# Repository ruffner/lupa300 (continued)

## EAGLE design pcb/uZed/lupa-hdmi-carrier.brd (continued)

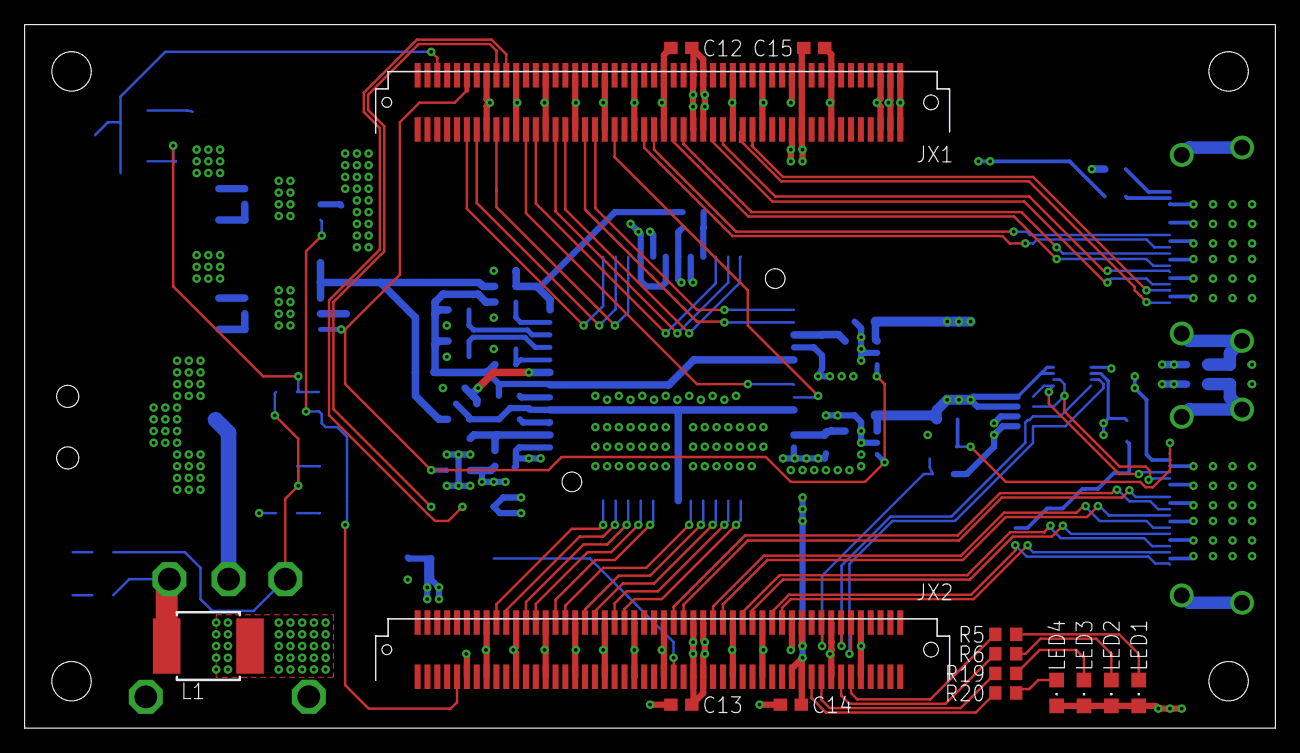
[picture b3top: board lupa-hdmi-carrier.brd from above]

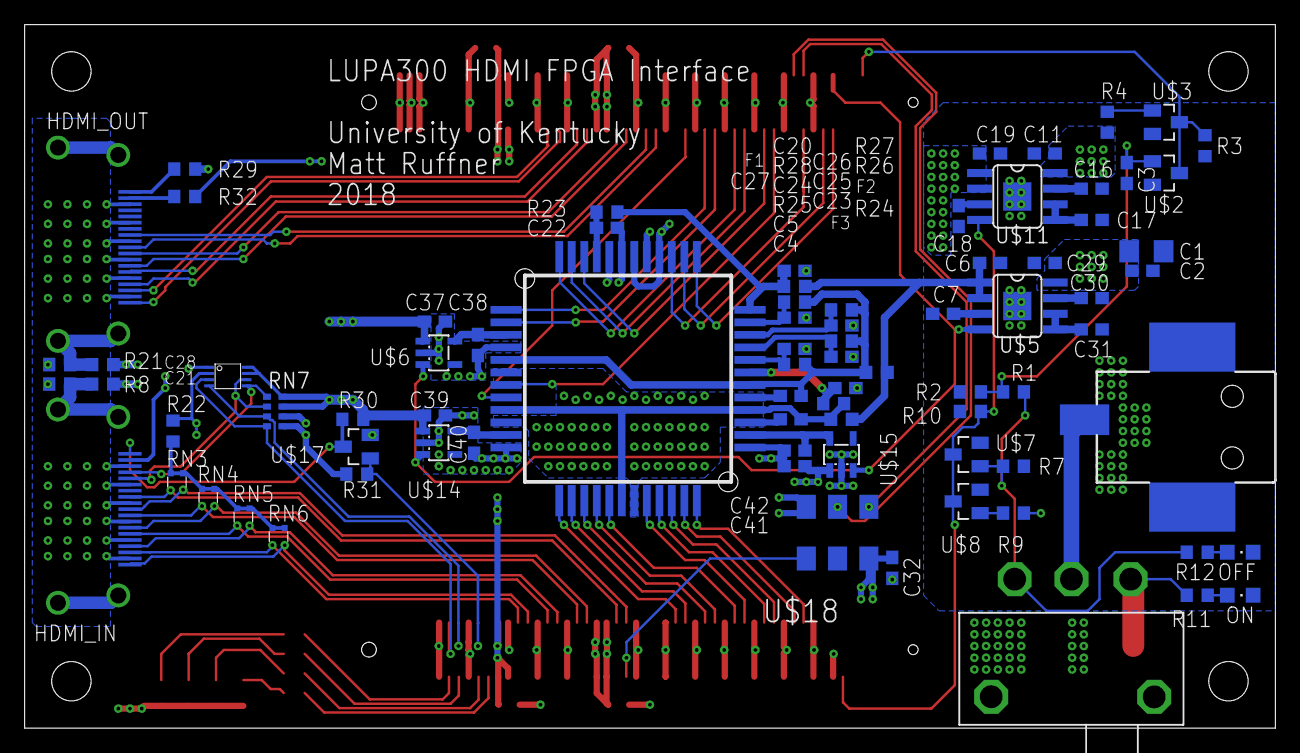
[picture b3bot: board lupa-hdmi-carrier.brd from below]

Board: 4 copper layers, 101.6 x 57.1 mm, 95 parts (80 on the bottom side), 91 nets.

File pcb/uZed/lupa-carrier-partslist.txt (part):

Partlist

Exported from lupa-carrier.sch at 7/17/2018 12:01 PM

EAGLE Version 9.0.1 Copyright (c) 1988-2018 Autodesk, Inc.

Assembly variant: 

Part     Value                   Device                  Package      Library                                                          Sheet

C1       22uF                    C-USC1206               C1206        rcl                                                              2
C2       .1uF                    C-USC0603               C0603        rcl                                                              2
C3       .1uF                    C-USC0603               C0603        rcl                                                              2
C4       1uF                     C-USC0603               C0603        rcl                                                              4
C5       1uF                     C-USC0603               C0603        rcl                                                              4
C6       10uF                    C-USC0603               C0603        rcl                                                              4
C7       1uF                     C-USC0603               C0603        rcl                                                              4
C8       .1uF                    C-USC0603               C0603        rcl                                                              2
C9       .1uF                    C-USC0603               C0603        rcl                                                              2
C10      .1uF                    C-USC0603               C0603        rcl                                                              2
C11      10uF                    C-USC0603               C0603        rcl                                                              2
C12      .1uF                    C-USC0603               C0603        rcl                                                              1
C13      .1uF                    C-USC0603               C0603        rcl                                                              1
C14      .1uF                    C-USC0603               C0603        rcl                                                              1
C15      .1uF                    C-USC0603               C0603        rcl                                                              1
C16      1uF                     C-USC0603               C0603        rcl                                                              2
C17      1uF                     C-USC0603               C0603        rcl                                                              2
C18      1uF                     C-USC0603               C0603        rcl                                                              2
C19      10uF                    C-USC0603               C0603        rcl                                                              2
C20      1uF                     C-USC0603               C0603        rcl                                                              4
C22      .1uF                    C-EUC0603               C0603        rcl                                                              3
C23      .1uF                    C-EUC0603               C0603        rcl                                                              3
C24      .1uf                    C-EUC0603               C0603        rcl                                                              3
C25      .1uf                    C-EUC0603               C0603        rcl                                                              3
C26      .1uF                    C-EUC0603               C0603        rcl                                                              3
C27      .1uF                    C-EUC0603               C0603        rcl                                                              3
C29      10uF                    C-USC0603               C0603        rcl                                                              4
C30      1uF                     C-USC0603               C0603        rcl                                                              4
C31      1uF                     C-USC0603               C0603        rcl                                                              4
C37      1uF                     C-USC0603               C0603        rcl                                                              4
C38      1uF                     C-USC0603               C0603        rcl                                                              4
C39      1uF                     C-USC0603               C0603        rcl                                                              4
C40      1uF                     C-USC0603               C0603        rcl                                                              4
C41      1uF                     C-USC0603               C0603        rcl                                                              4
C42      1uF                     C-USC0603               C0603        rcl                                                              4
FR_VAL   TPTP08R                 TPTP08R                 TP08R        testpad                                                          3
INT1     TPTP08R                 TPTP08R                 TP08R        testpad                                                          3
INT2     TPTP08R                 TPTP08R                 TP08R        testpad                                                          3
INT3     TPTP08R                 TPTP08R                 TP08R        testpad                                                          3
JX1      BERGSTAK-100POS         BERGSTAK-100POS         BERG100POS   lupa300-components                                               1
JX2      BERGSTAK-100POS         BERGSTAK-100POS         BERG100POS   lupa300-components                                               1
K1       694108105102            694108105102            694108105102 Wurth_Elektronik_Electromechanic_DC_Power_Jack_Connectors_rev15c 2
LED1                             LEDCHIPLED_0805         CHIPLED_0805 led                                                              1
LED2                             LEDCHIPLED_0805         CHIPLED_0805 led                                                              1
LED3                             LEDCHIPLED_0805         CHIPLED_0805 led                                                              1
LED4                             LEDCHIPLED_0805         CHIPLED_0805 led                                                              1
LN_VAL   TPTP08R                 TPTP08R                 TP08R        testpad                                                          3
POW_EN   TPTP08R                 TPTP08R                 TP08R        testpad                                                          1
R1       1k                      R-US_R0603              R0603        rcl                                                              2
R2       3k92                    R-US_R0603              R0603        rcl                                                              2
R3       430                     R-US_R0603              R0603        rcl                                                              2
R4       680                     R-US_R0603              R0603        rcl                                                              2
R5       330                     R-US_R0603              R0603        resistor                                                         1
R6       330                     R-US_R0603              R0603        resistor                                                         1
R7       3k92                    R-US_R0603              R0603        rcl                                                              2
R9       220                     R-US_R0603              R0603        rcl                                                              2
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
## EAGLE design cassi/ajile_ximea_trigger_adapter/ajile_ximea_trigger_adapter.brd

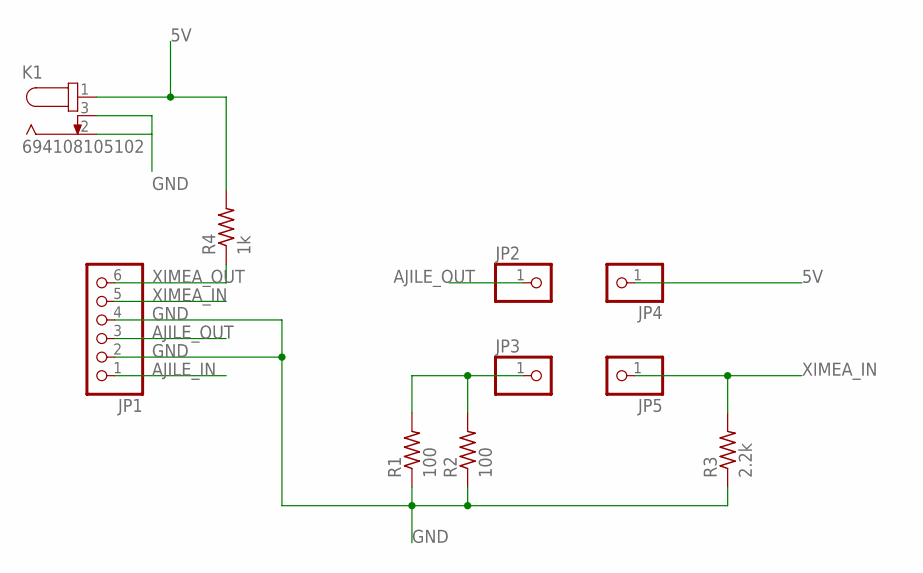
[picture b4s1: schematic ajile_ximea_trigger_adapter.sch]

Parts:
JP1: PINHD-1X6; 1X06
JP2, JP3, JP4, JP5: PINHD-1X1; 1X01
K1: 694108105102
R1, R2: 100; 0204/7
R3: 2.2k; 0204/7
R4: 1k; 0204/7

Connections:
5V: JP4.1, K1.1, R4.2
AJILE_IN: JP1.1
AJILE_OUT: JP1.3, JP2.1
GND: JP1.2, JP1.4, K1.2, K1.3, R1.1, R2.1, R3.1
unnamed: JP3.1, R1.2, R2.2
XIMEA_IN: JP1.5, JP5.1, R3.2
XIMEA_OUT: JP1.6, R4.1

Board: 2 copper layers, 10 parts (0 on the bottom side), 6 nets, no tracks yet.

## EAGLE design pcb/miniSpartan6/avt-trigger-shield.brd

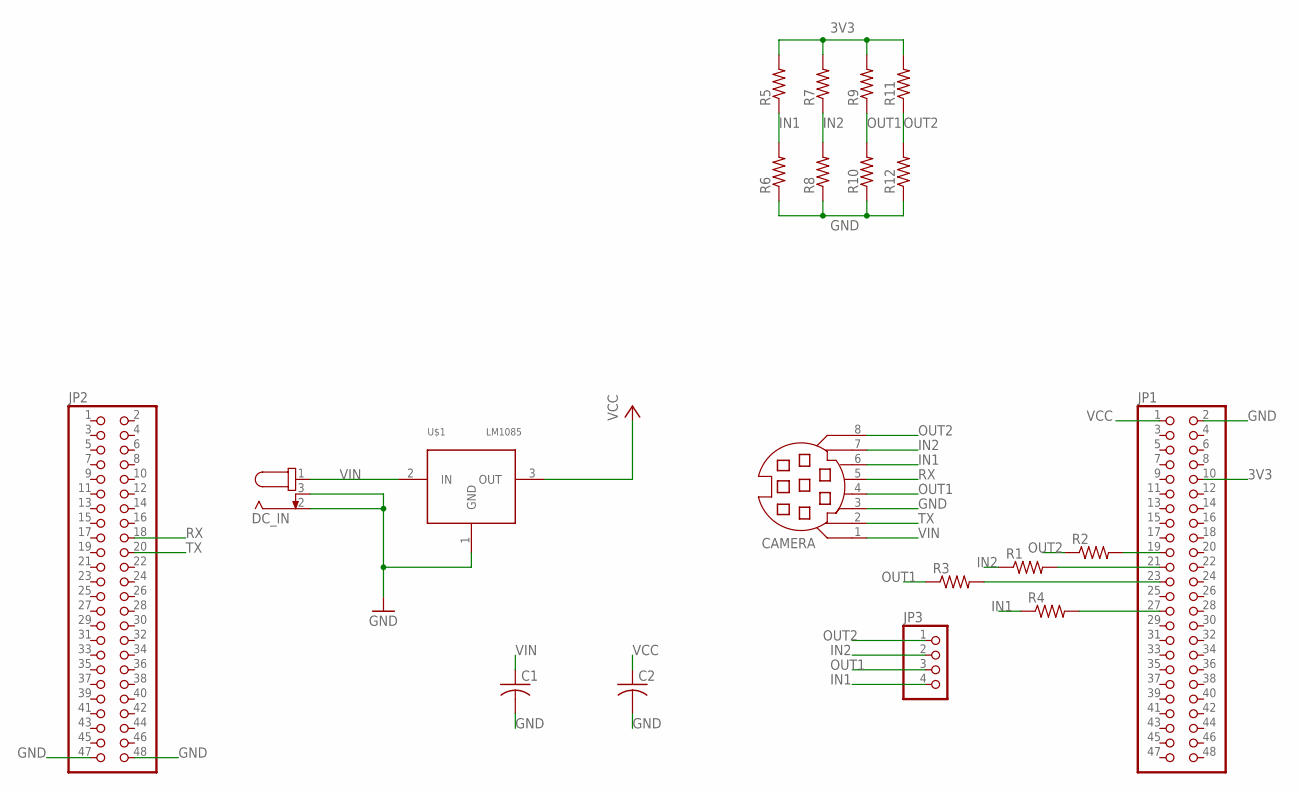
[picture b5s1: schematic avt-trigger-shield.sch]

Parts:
C1, C2: C-USC1206; C1206
CAMERA: MD08SS; MDIN08SS
DC_IN: 694106105102
JP1, JP2: PINHD-2X24; 2X24
JP3: PINHD-1X4; 1X04
R1, R2, R3, R4, R5, R6, R7, R8, R9, R10, R11, R12: R-US_R0603; R0603
U$1: LM1085; TO263

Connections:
3V3: JP1.10, R5.2, R7.2, R9.2, R11.2
GND: C1.2, C2.2, CAMERA.3, DC_IN.2, DC_IN.3, JP1.2, JP2.47, JP2.48, R6.1, R8.1, R10.1, R12.1, U$1.1 (GND)
IN1: CAMERA.6, JP3.4, R4.1, R5.1, R6.2
IN2: CAMERA.7, JP3.2, R1.1, R7.1, R8.2
unnamed: JP1.21, R1.2
unnamed: JP1.19, R2.2
unnamed: JP1.23, R3.2
unnamed: JP1.27, R4.2
OUT1: CAMERA.4, JP3.3, R3.1, R9.1, R10.2
OUT2: CAMERA.8, JP3.1, R2.1, R11.1, R12.2
RX: CAMERA.5, JP2.18
TX: CAMERA.2, JP2.20
VCC: C2.1, JP1.1, U$1.3 (OUT)
VIN: C1.1, CAMERA.1, DC_IN.1, U$1.2 (IN)

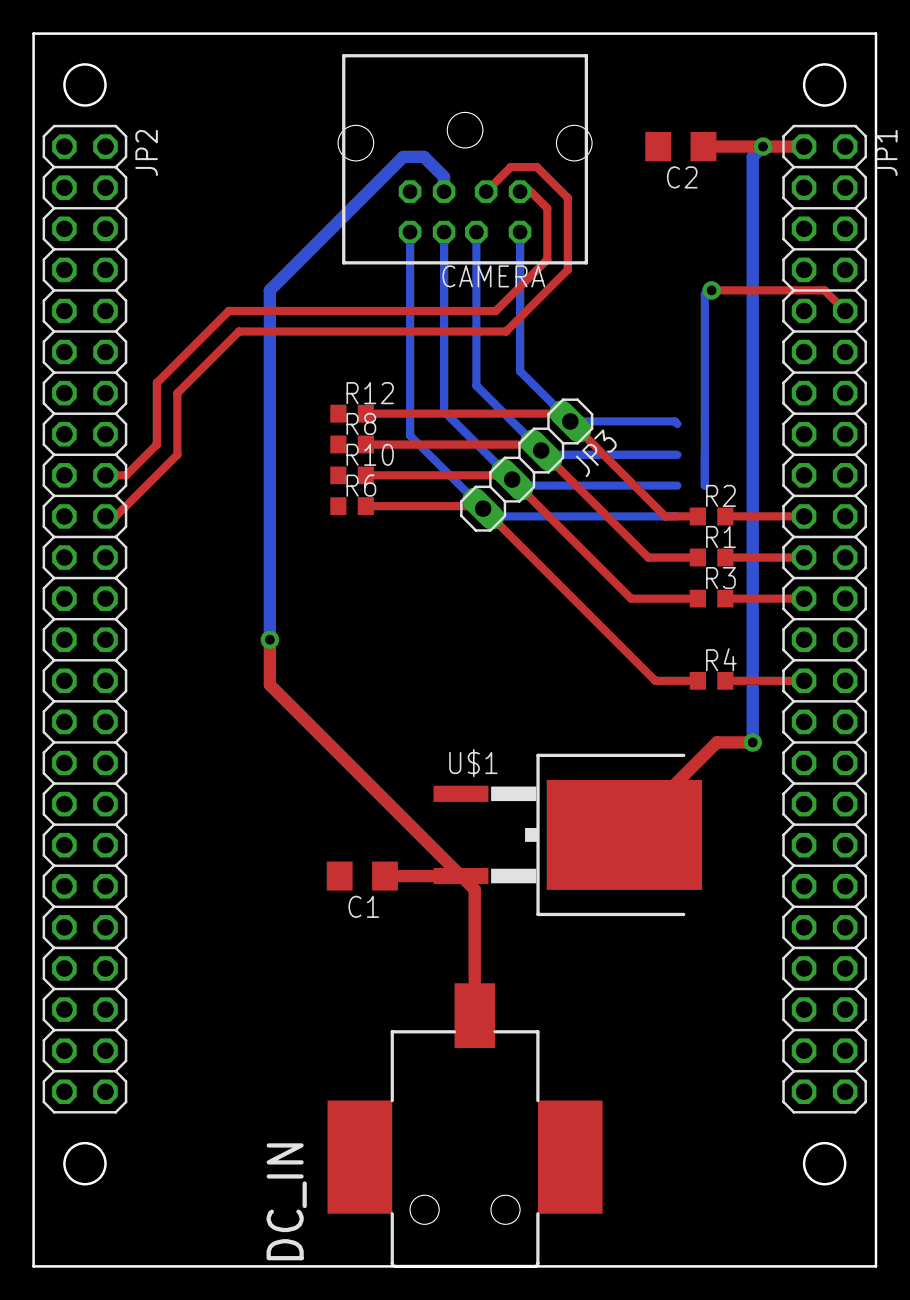
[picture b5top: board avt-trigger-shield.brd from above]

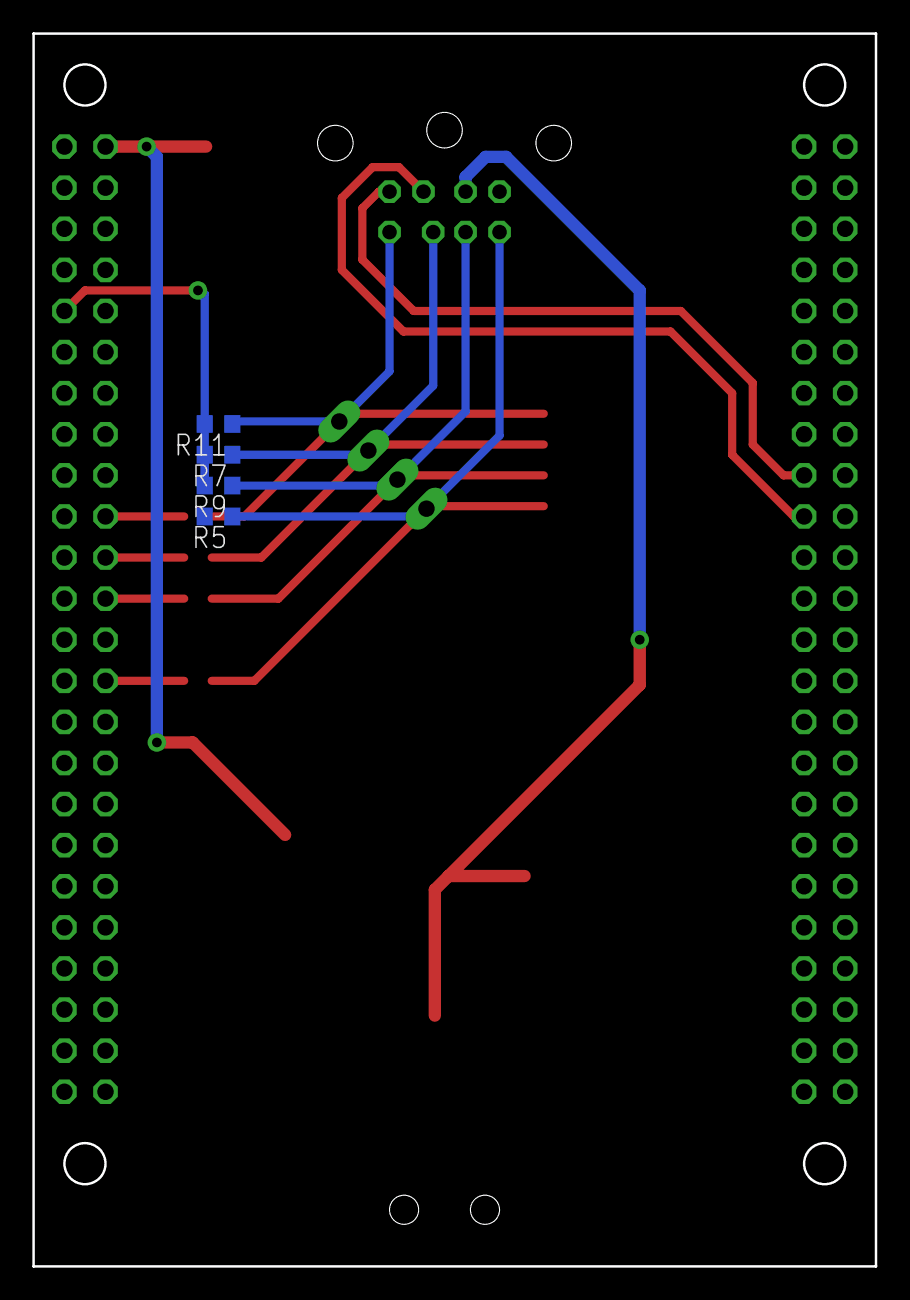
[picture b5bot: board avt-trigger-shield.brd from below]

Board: 2 copper layers, 52.1 x 76.2 mm, 20 parts (4 on the bottom side), 14 nets.

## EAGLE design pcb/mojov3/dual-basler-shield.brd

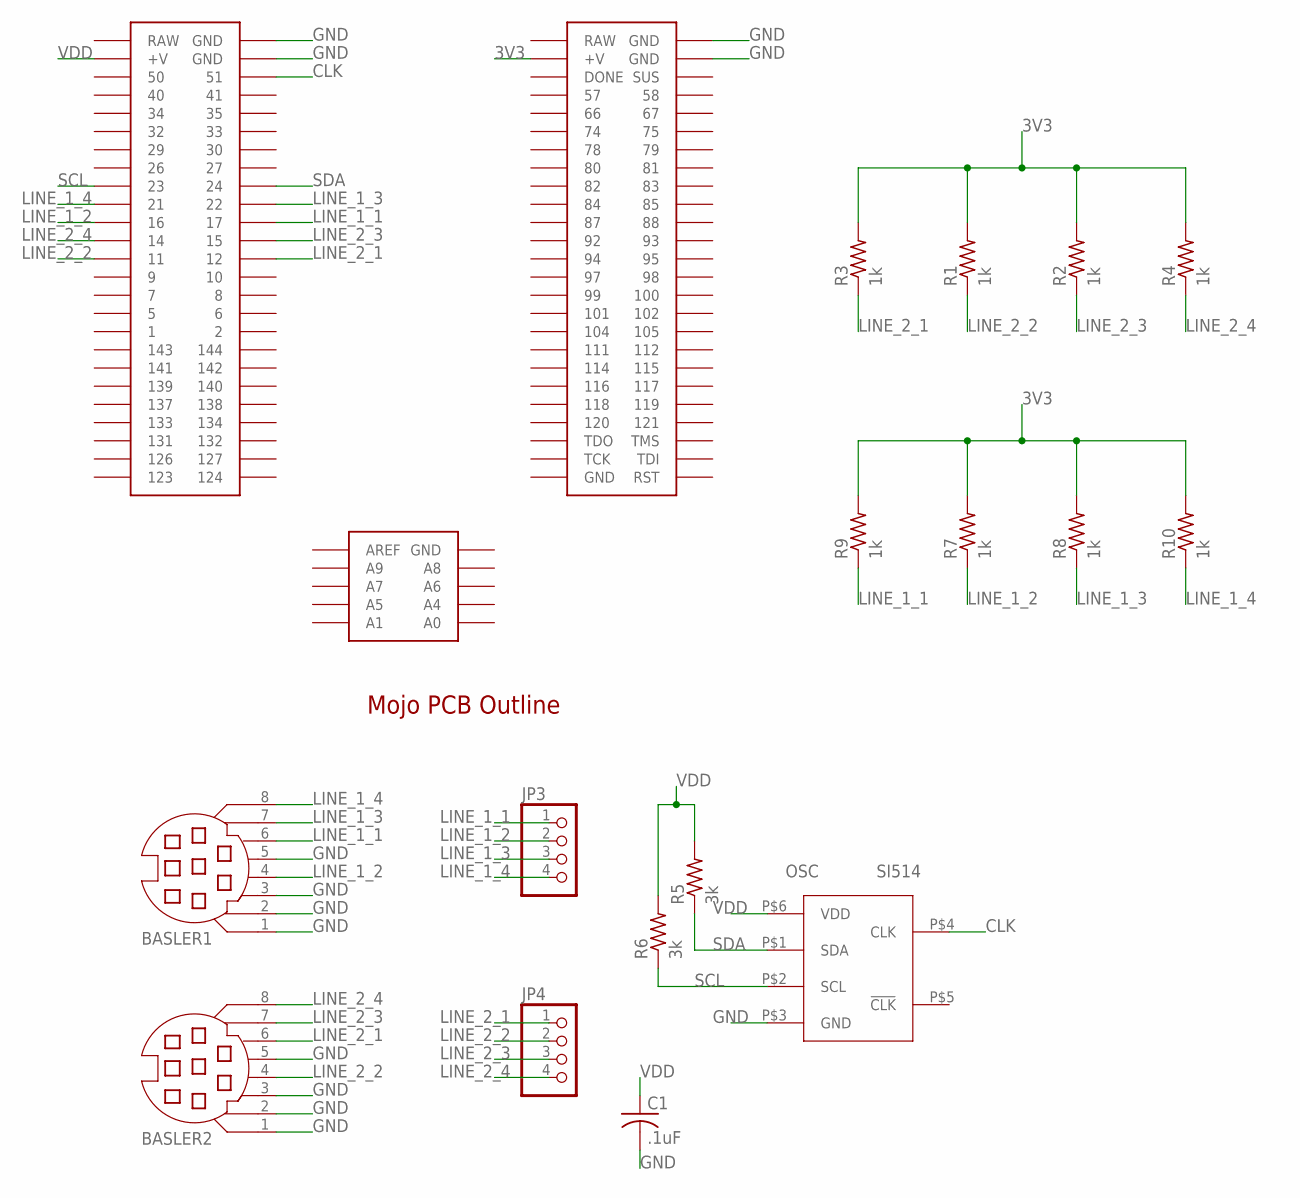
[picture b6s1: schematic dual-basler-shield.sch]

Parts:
BASLER1, BASLER2: MD08SS; MDIN08SS
C1: .1uF; C0603
JP3, JP4: PINHD-1X4; 1X04
OSC: SI514; XTAL-6PIN
R1, R2, R3, R4, R7, R8, R9, R10: 1k; R0603
R5, R6: 3k; R0603
U$3: MOJO_OUTLINE
U$4: MOJOV3; MOJO_V3

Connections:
3V3: R1.2, R2.2, R3.2, R4.2, R7.2, R8.2, R9.2, R10.2, U$4.V@2 (+V)
CLK: OSC.P$4 (CLK), U$4.51
GND: BASLER1.1, BASLER1.2, BASLER1.3, BASLER1.5, BASLER2.1, BASLER2.2, BASLER2.3, BASLER2.5, C1.2, OSC.P$3 (GND), U$4.GND@1 (GND), U$4.GND@2 (GND), U$4.GND@3 (GND), U$4.GND@4 (GND)
LINE_1_1: BASLER1.6, JP3.1, R9.1, U$4.17
LINE_1_2: BASLER1.4, JP3.2, R7.1, U$4.16
LINE_1_3: BASLER1.7, JP3.3, R8.1, U$4.22
LINE_1_4: BASLER1.8, JP3.4, R10.1, U$4.21
LINE_2_1: BASLER2.6, JP4.1, R3.1, U$4.12
LINE_2_2: BASLER2.4, JP4.2, R1.1, U$4.11
LINE_2_3: BASLER2.7, JP4.3, R2.1, U$4.15
LINE_2_4: BASLER2.8, JP4.4, R4.1, U$4.14
SCL: OSC.P$2 (SCL), R6.1, U$4.23
SDA: OSC.P$1 (SDA), R5.1, U$4.24
VDD: C1.1, OSC.P$6 (VDD), R5.2, R6.2, U$4.V@1 (+V)

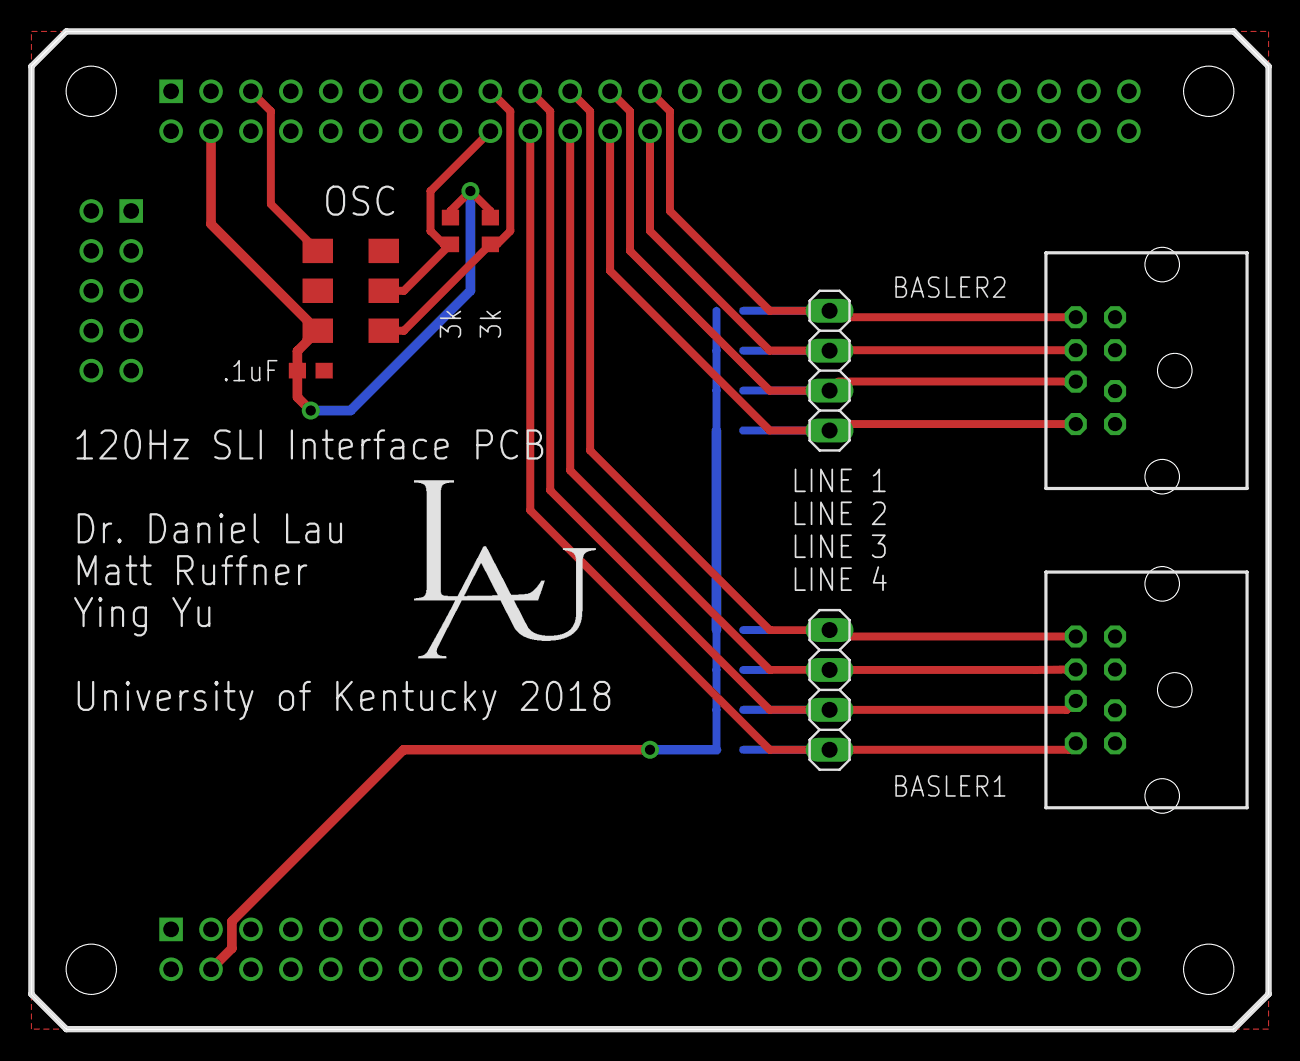
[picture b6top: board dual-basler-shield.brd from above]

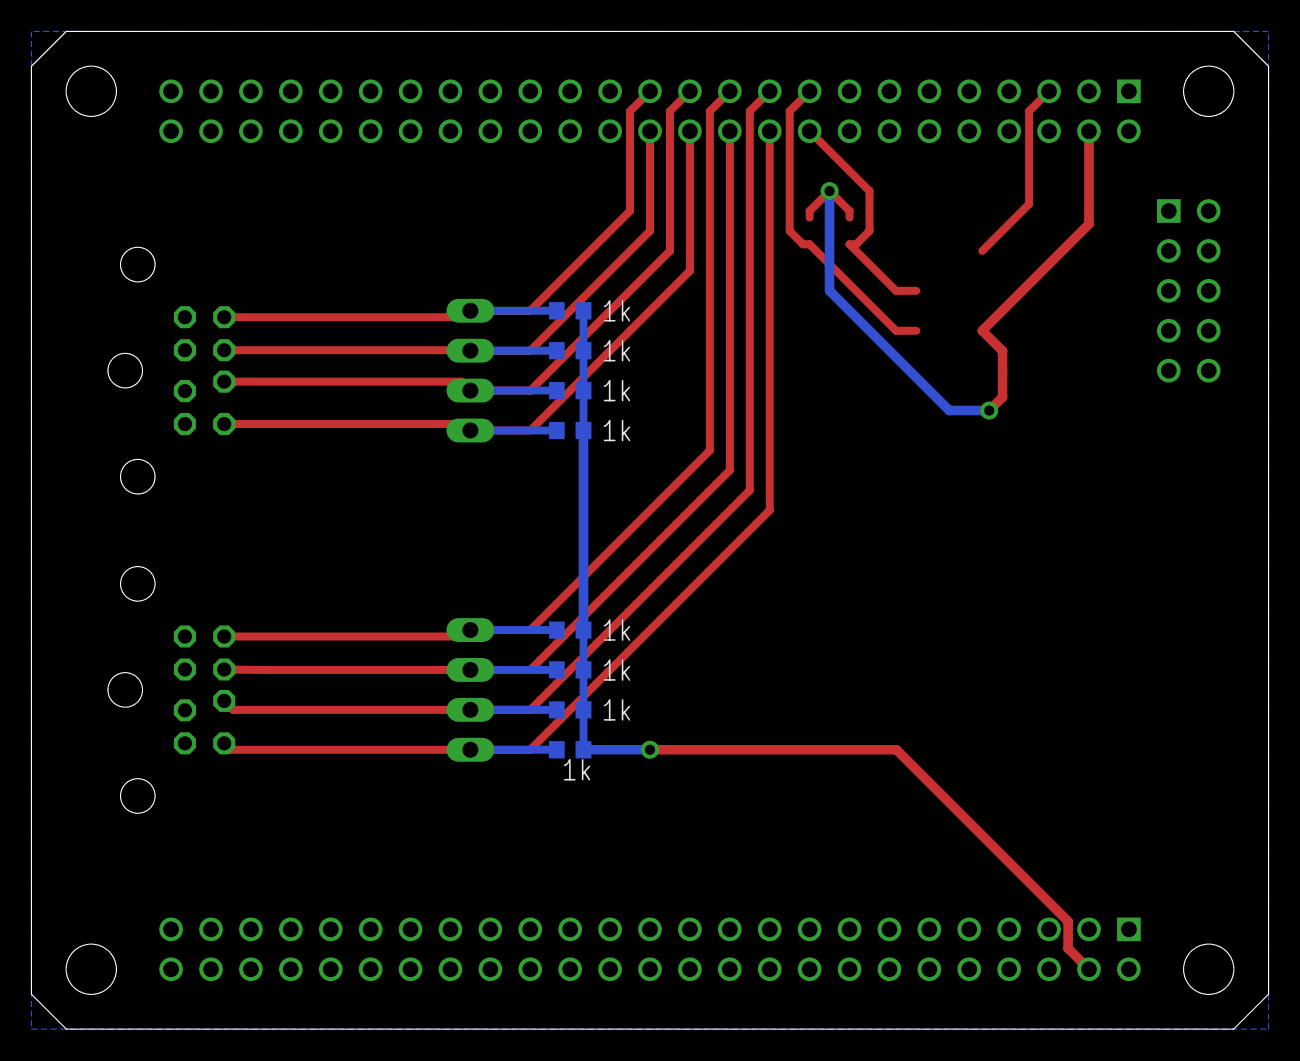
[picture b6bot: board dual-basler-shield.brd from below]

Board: 2 copper layers, 78.7 x 63.5 mm, 18 parts (8 on the bottom side), 14 nets.

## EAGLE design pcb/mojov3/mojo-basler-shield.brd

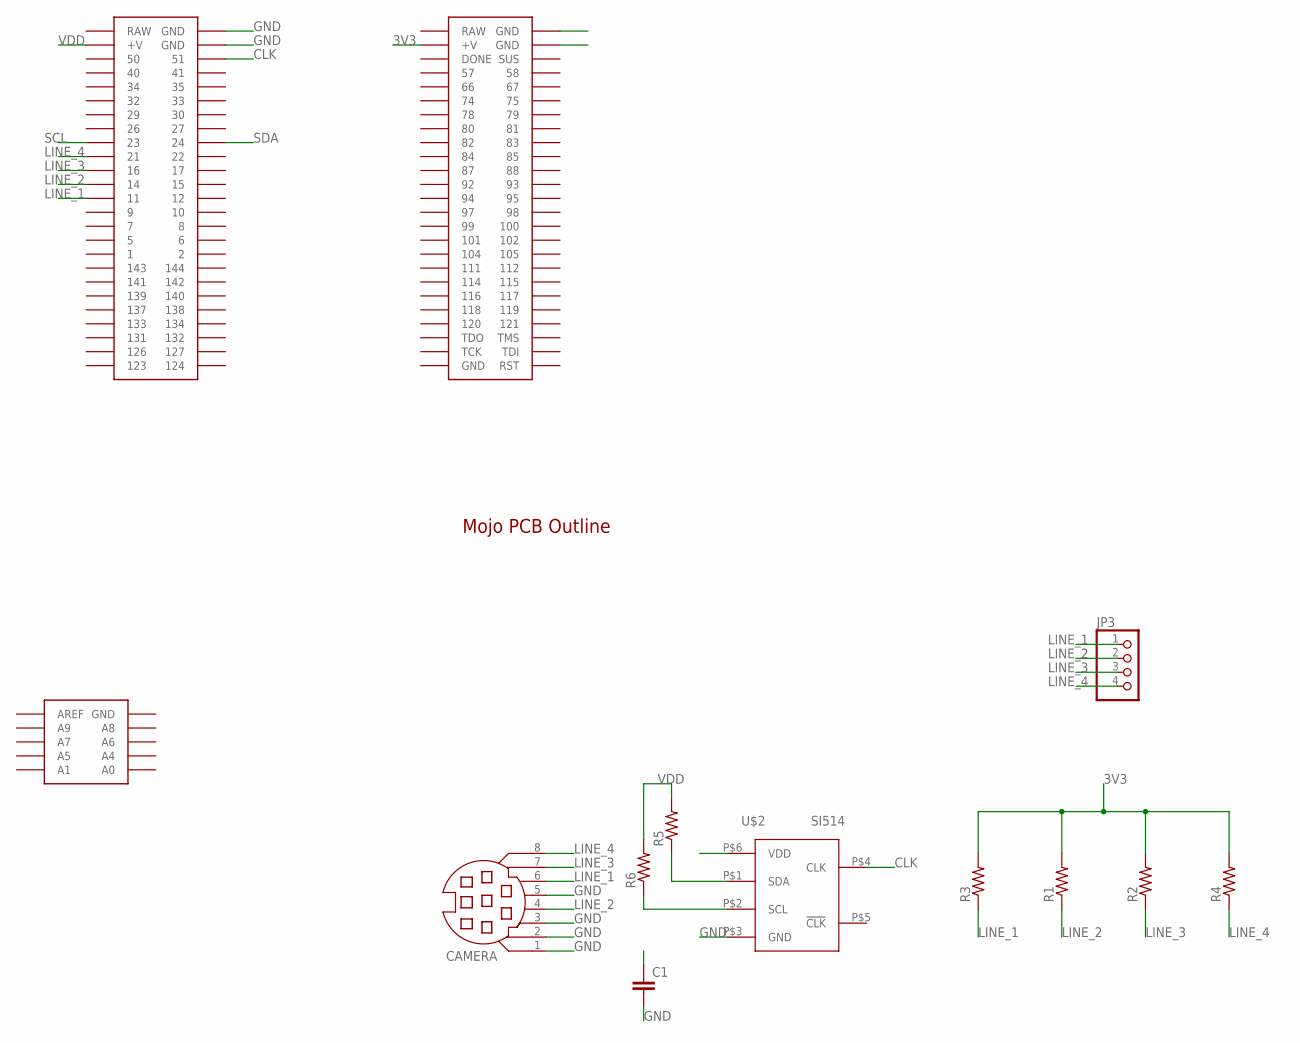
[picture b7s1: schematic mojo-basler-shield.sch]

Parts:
C1: C-EUC0603; C0603
CAMERA: MD08SS; MDIN08SS
JP3: PINHD-1X4; 1X04
R1, R2, R3, R4, R5, R6: R-US_R0603; R0603
U$1: MOJO_OUTLINE
U$2: SI514; XTAL-6PIN
U$3: MOJOV3; MOJO_V3

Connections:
3V3: R1.2, R2.2, R3.2, R4.2, U$3.V@2 (+V)
CLK: U$2.P$4 (CLK), U$3.51
GND: C1.2, CAMERA.1, CAMERA.2, CAMERA.3, CAMERA.5, U$2.P$3 (GND), U$3.GND@1 (GND), U$3.GND@2 (GND), U$3.GND@3 (GND), U$3.GND@4 (GND)
LINE_1: CAMERA.6, JP3.1, R3.1, U$3.11
LINE_2: CAMERA.4, JP3.2, R1.1, U$3.14
LINE_3: CAMERA.7, JP3.3, R2.1, U$3.16
LINE_4: CAMERA.8, JP3.4, R4.1, U$3.21
SCL: R6.1, U$2.P$2 (SCL), U$3.23
SDA: R5.1, U$2.P$1 (SDA), U$3.24
VDD: C1.1, R5.2, R6.2, U$2.P$6 (VDD), U$3.V@1 (+V)

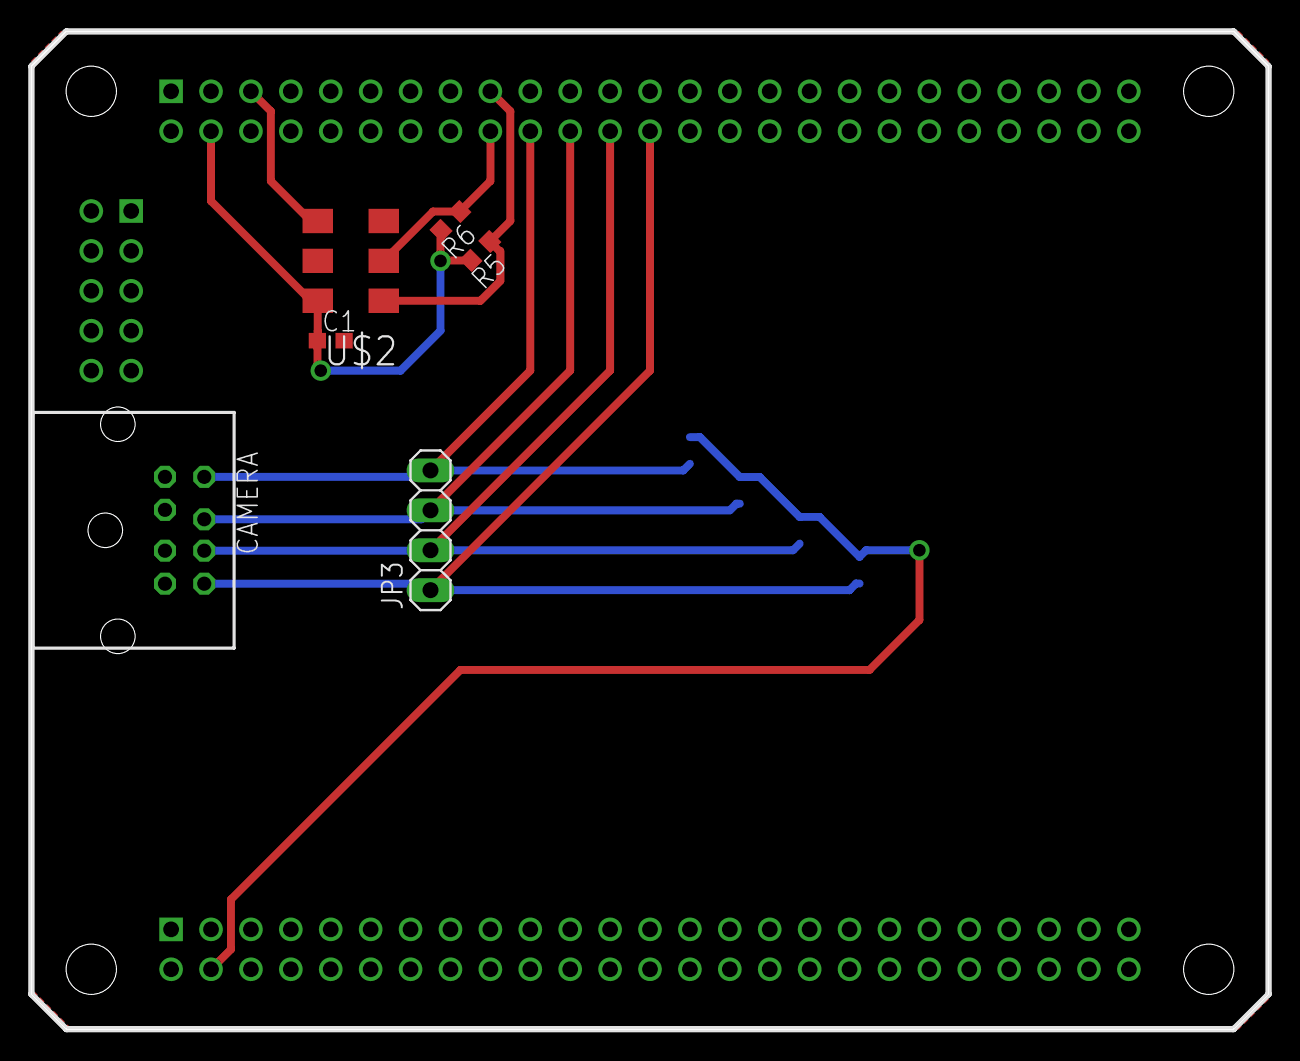
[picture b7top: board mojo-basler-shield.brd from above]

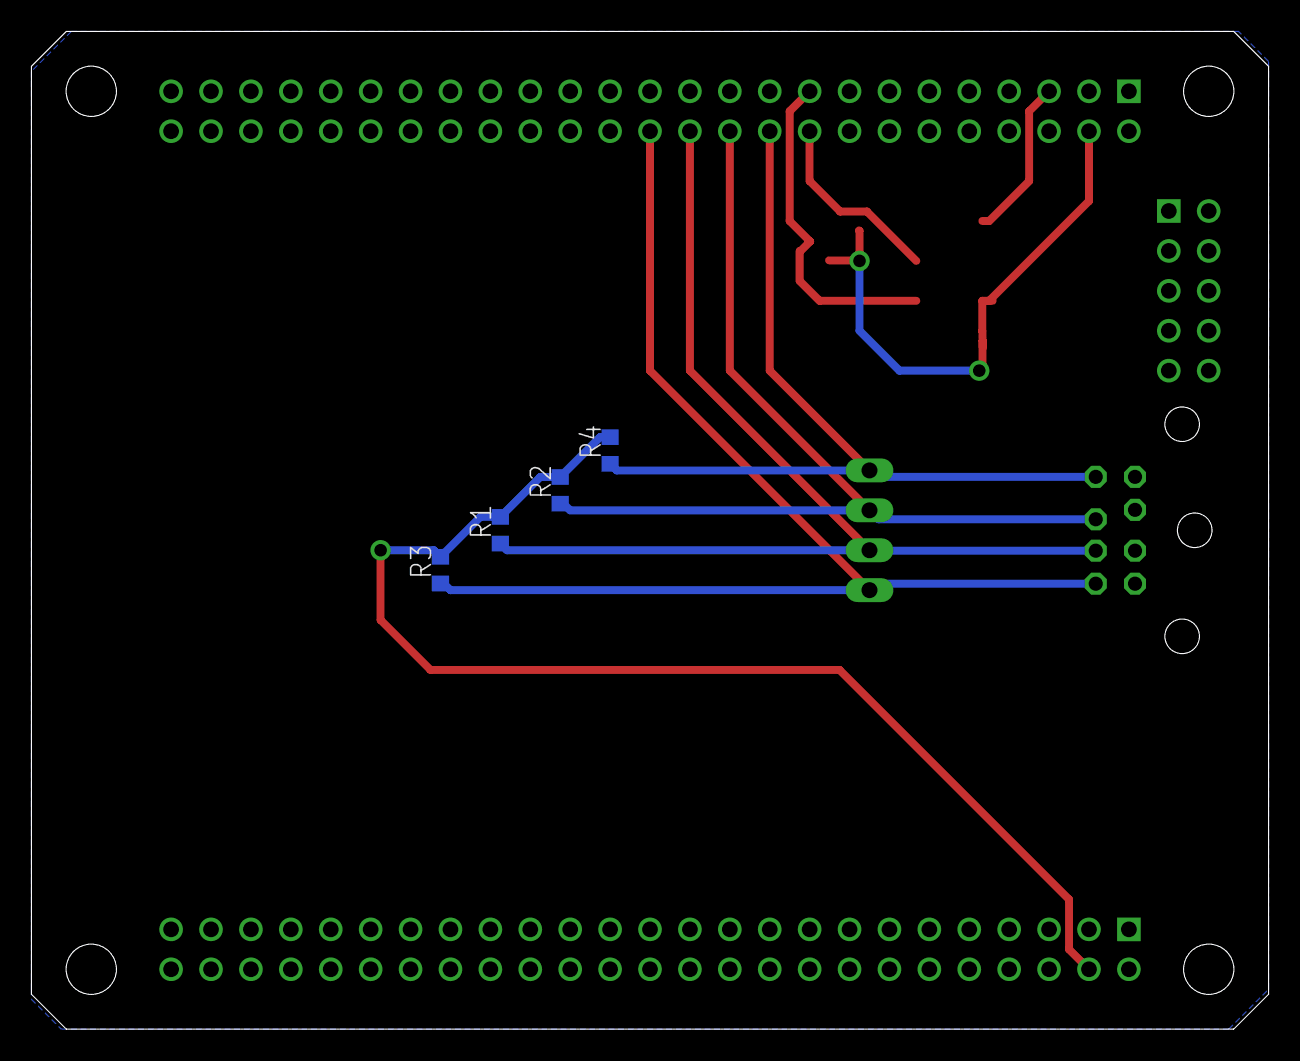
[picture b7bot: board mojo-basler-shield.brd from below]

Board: 2 copper layers, 78.7 x 63.5 mm, 12 parts (4 on the bottom side), 10 nets.
